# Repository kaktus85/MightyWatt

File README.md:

# MightyWatt
Resources for MightyWatt electronic load.
This repository contains all the available documentation and source files for MightyWatt electronic load project.
- a copy of this is also available on Google Drive: https://drive.google.com/folderview?id=0B7G3xJXZNLUpfnVWSEF0VTA3WkxmOUZ6U2pOcVNRdFloU2d0UzdjeE5NdHU3R0FZb3NNR2c&usp=sharing
- an easy to read description of the various folders is here: http://kaktuscircuits.blogspot.cz/2015/03/mightywatt-resource-page.html
- MightyWatt can be purchased through Tindie: https://www.tindie.com/products/Kaktus/mightywatt-kit-70w-electronic-load-for-arduino/

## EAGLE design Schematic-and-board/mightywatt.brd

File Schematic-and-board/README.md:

# Schematic and Board
- Cadsoft Eagle source files for the PCB of MightyWatt.
- A PNG schematic also included for a quick reference without having to install Eagle.

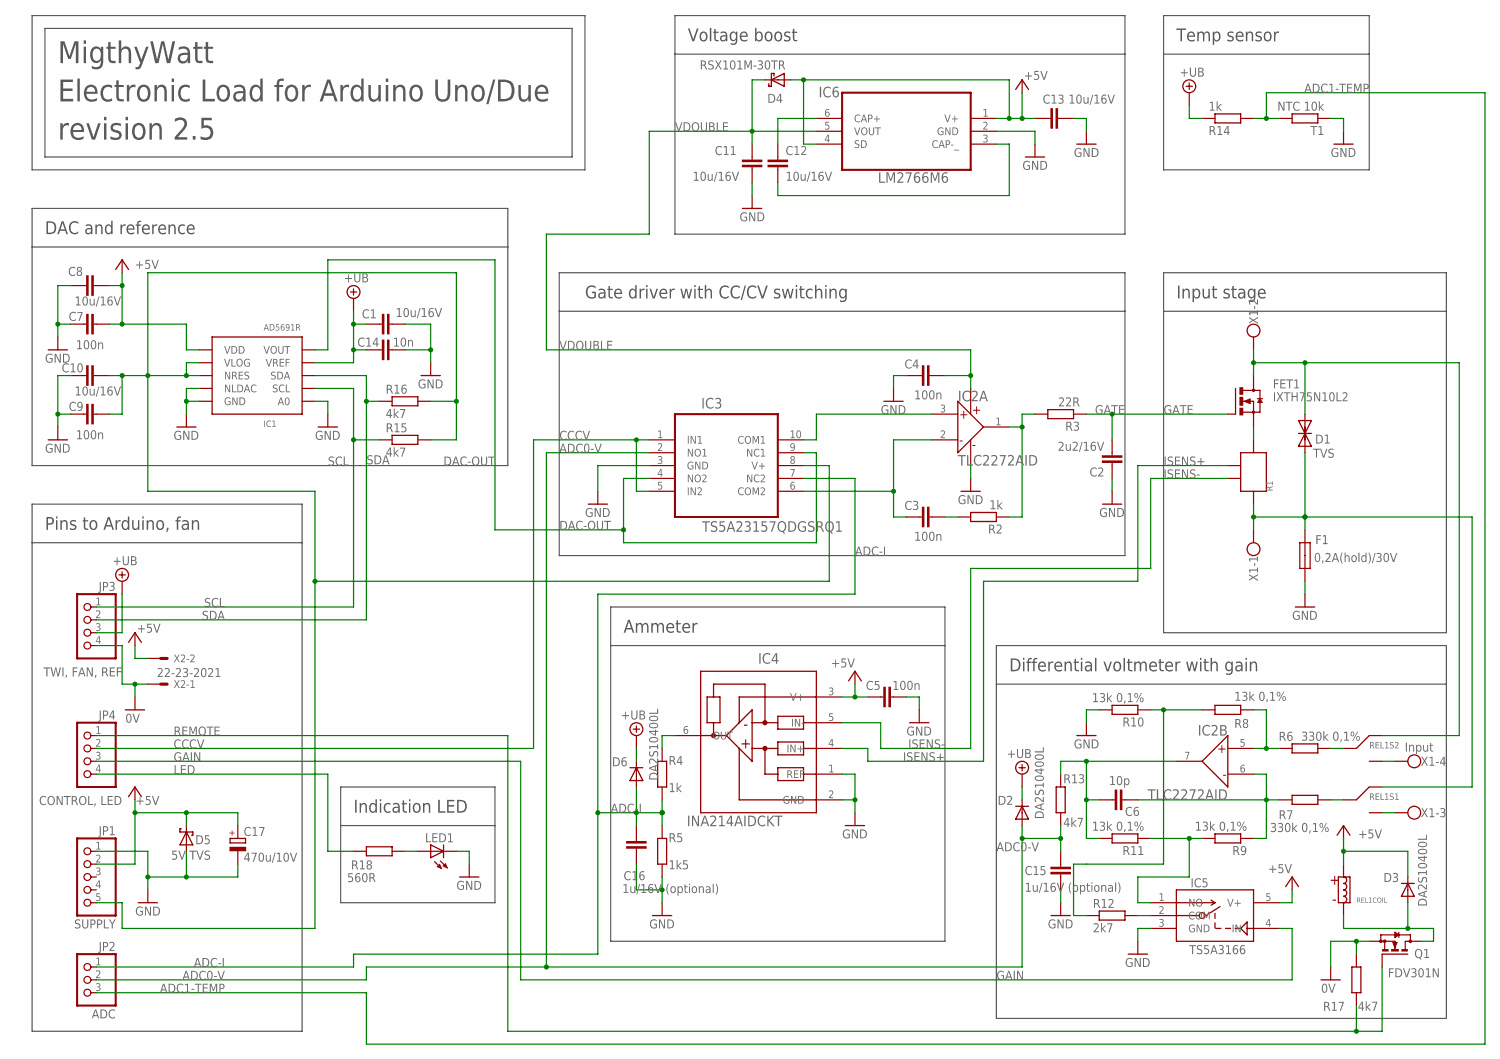
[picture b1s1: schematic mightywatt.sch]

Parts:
C1, C8, C10, C11, C12, C13: 10u/16V; C1206
C2: 2u2/16V; C1206
C3, C4, C5, C7, C9: 100n; C0603
C6: 10p; C0603
C14: 10n; C0805
C15, C16: 1u/16V (optional); C0603
C17: 470u/10V; SMC_E
D1: TVS; SMC
D2, D3, D6: DA2S10400L; SOD523
D4: RSX101M-30TR; SOD123
D5: 5V TVS; SMB
F1: 0,2A(hold)/30V; R1812
FET1: IXTH75N10L2; TO-247AD-H
IC1: AD5691RAD5691R; SOP50P490X110-10N
IC2: TLC2272AID; SOIC127P600X175-8N
IC3: TS5A23157QDGSRQ1; SOP50P490X110-10N
IC4: INA214AIDCKT; SOT65P210X110-6N; MPN INA214BIDCKT
IC5: TS5A3166; SC70-5
IC6: LM2766M6; SOT95P285X122-6N
JP1: SUPPLY; 1X05
JP2: ADC; 1X03
JP3: TWI, FAN, REF; 1X04
JP4: CONTROL, LED; 1X04
LED1: LEDCHIP-LED0805; CHIP-LED0805
Q1: BSS123; SOT23; PARTNAME FDV301N
R1: WSL3637; POWER-R-4TERM
R2, R4, R14: 1k; R0603
R3: 22R; R0603
R5: 1k5; R0603
R6, R7: 330k 0,1%; R0603
R8, R9, R10, R11: 13k 0,1%; R0603
R12: 2k7; R0603
R13, R15, R16, R17: 4k7; R0603
R18: 560R; R0603
REL1: IM03NS; IM03NS-NARROW-RELAY
T1: NTC 10k; R0402
X1: Input; W237-4
X2: 22-23-2021

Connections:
0V: JP3.4, Q1.2 (S), R17.1, X2.1
+5V: C5.1, C7.2, C8.2, C13.1, C17.+, D3.C, D4.A, D5.C, IC1.1 (VDD), IC4.3 (V+), IC5.5 (V+), IC6.1 (V+), IC6.4 (SD), JP1.2, REL1.P$1 (C+), X2.2
+UB: C1.1, C14.1, D2.C, D6.C, IC1.9 (VREF), JP3.3, R14.1
ADC0-V: C15.2, D2.A, IC3.2 (NO1), JP2.2, R13.1
ADC1-TEMP: JP2.3, R14.2, T1.2
ADC-I: C16.2, D6.A, IC3.7 (NC2), JP2.1, R4.2, R5.1
CCCV: IC3.1 (IN1), IC3.5 (IN2), JP4.2
DAC-OUT: IC1.10 (VOUT), IC3.4 (NO2), IC3.9 (NC1)
GAIN: IC5.4 (IN), JP4.3
GATE: C2.2, FET1.G, R3.1
GND: C1.2, C2.1, C4.1, C5.2, C7.1, C8.1, C9.1, C10.1, C11.2, C13.2, C14.2, C15.1, C16.1, C17.-, D5.A, F1.2, IC1.4 (NLDAC), IC1.5 (GND), IC1.6 (A0), IC2.4 (V-/GND), IC3.3 (GND), IC4.1 (REF), IC4.2 (GND), IC5.3 (GND), IC6.2 (GND), JP1.1, LED1.C, R5.2, R10.2, T1.1
IOREF: C9.2, C10.2, IC1.2 (VLOG), IC1.3 (NRES), IC3.8 (V+), JP1.5, R15.2, R16.2
ISENS+: IC4.4 (IN+), R1.SENSE2
ISENS-: IC4.5 (IN-), R1.SENSE1
LED: JP4.4, R18.1
unnamed: IC2.5 (IN+), R6.2, R8.1
unnamed: D1.A, F1.1, R1.POWER1, REL1.P$2 (NC), X1.1
unnamed: C6.1, IC2.6 (IN-), R7.2, R9.1
unnamed: D1.C, FET1.D, REL1.P$7 (NC), X1.2
unnamed: C12.1, IC6.6 (CAP+)
unnamed: C12.2, IC6.3 (CAP-_)
unnamed: R8.2, R10.1, R12.1
unnamed: REL1.P$4 (NO), X1.3
unnamed: REL1.P$5 (NO), X1.4
unnamed: FET1.S, R1.POWER2
unnamed: IC2.1 (OUT), R2.1, R3.2
unnamed: R6.1, REL1.P$6 (COM)
unnamed: IC5.2 (COM), R12.2
unnamed: IC5.1 (NO), R9.2, R11.1
unnamed: LED1.A, R18.2
unnamed: R7.1, REL1.P$3 (COM)
unnamed: C3.2, R2.2
unnamed: C3.1, IC2.2 (IN-), IC3.6 (COM2)
unnamed: C6.2, IC2.7 (OUT), R11.2, R13.2
unnamed: IC2.3 (IN+), IC3.10 (COM1)
unnamed: D3.A, Q1.3 (D), REL1.P$8 (C-)
R3: IC4.6 (OUT), R4.1
REMOTE: JP4.1, Q1.1 (G), R17.2
SCL: IC1.7 (SCL), JP3.1, R15.1
SDA: IC1.8 (SDA), JP3.2, R16.1
VDOUBLE: C4.2, C11.1, D4.C, IC2.8 (V+), IC6.5 (VOUT)

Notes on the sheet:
Voltage boost
DAC and reference
Temp sensor
Pins to Arduino, fan
Input stage
Ammeter
Differential voltmeter with gain
Gate driver with CC/CV switching
MigthyWatt Electronic Load for Arduino Uno/Due revision 2.5
Indication LED

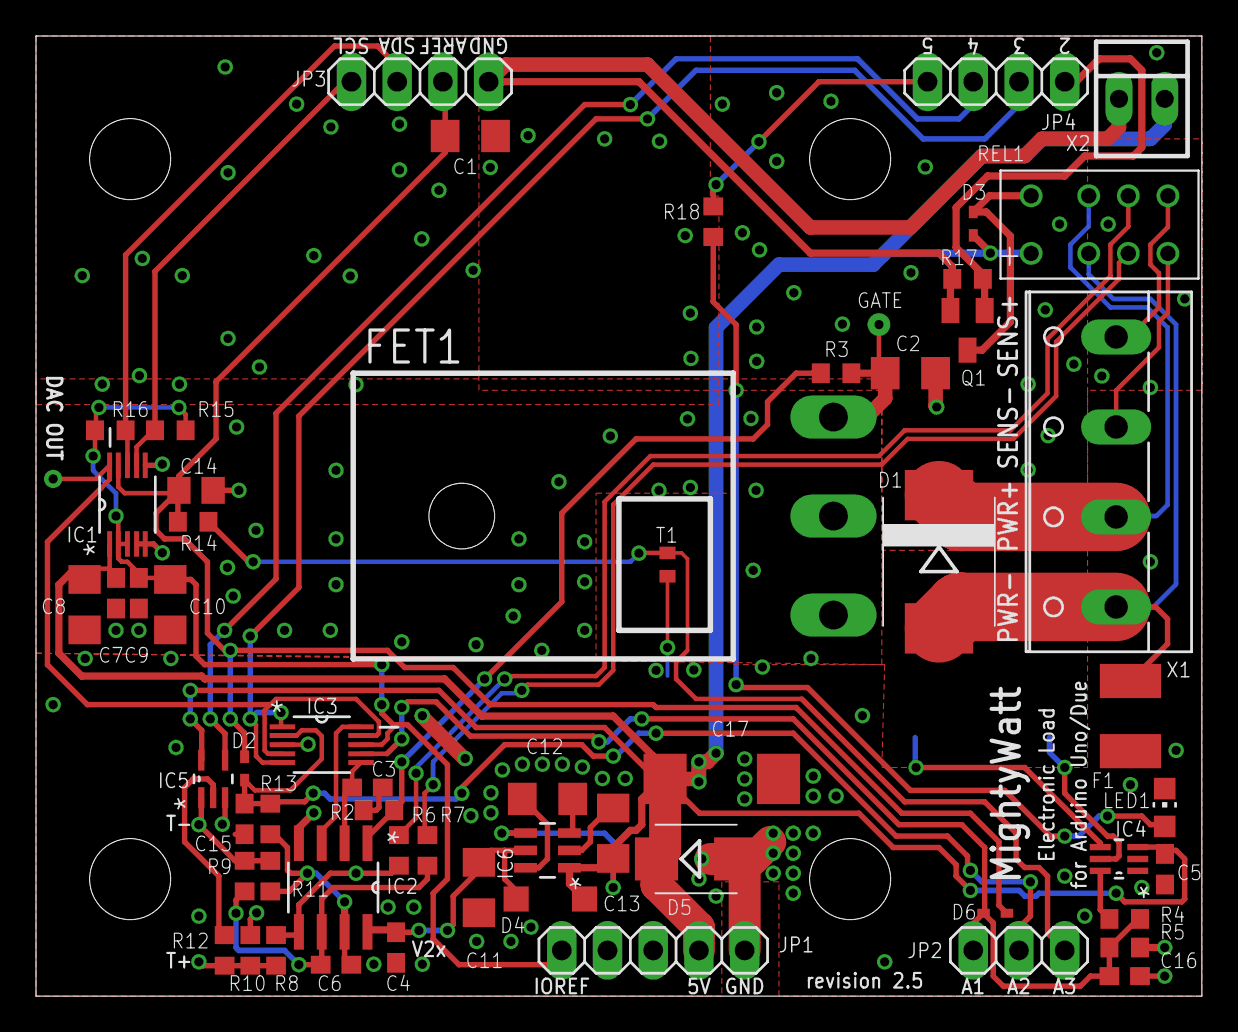
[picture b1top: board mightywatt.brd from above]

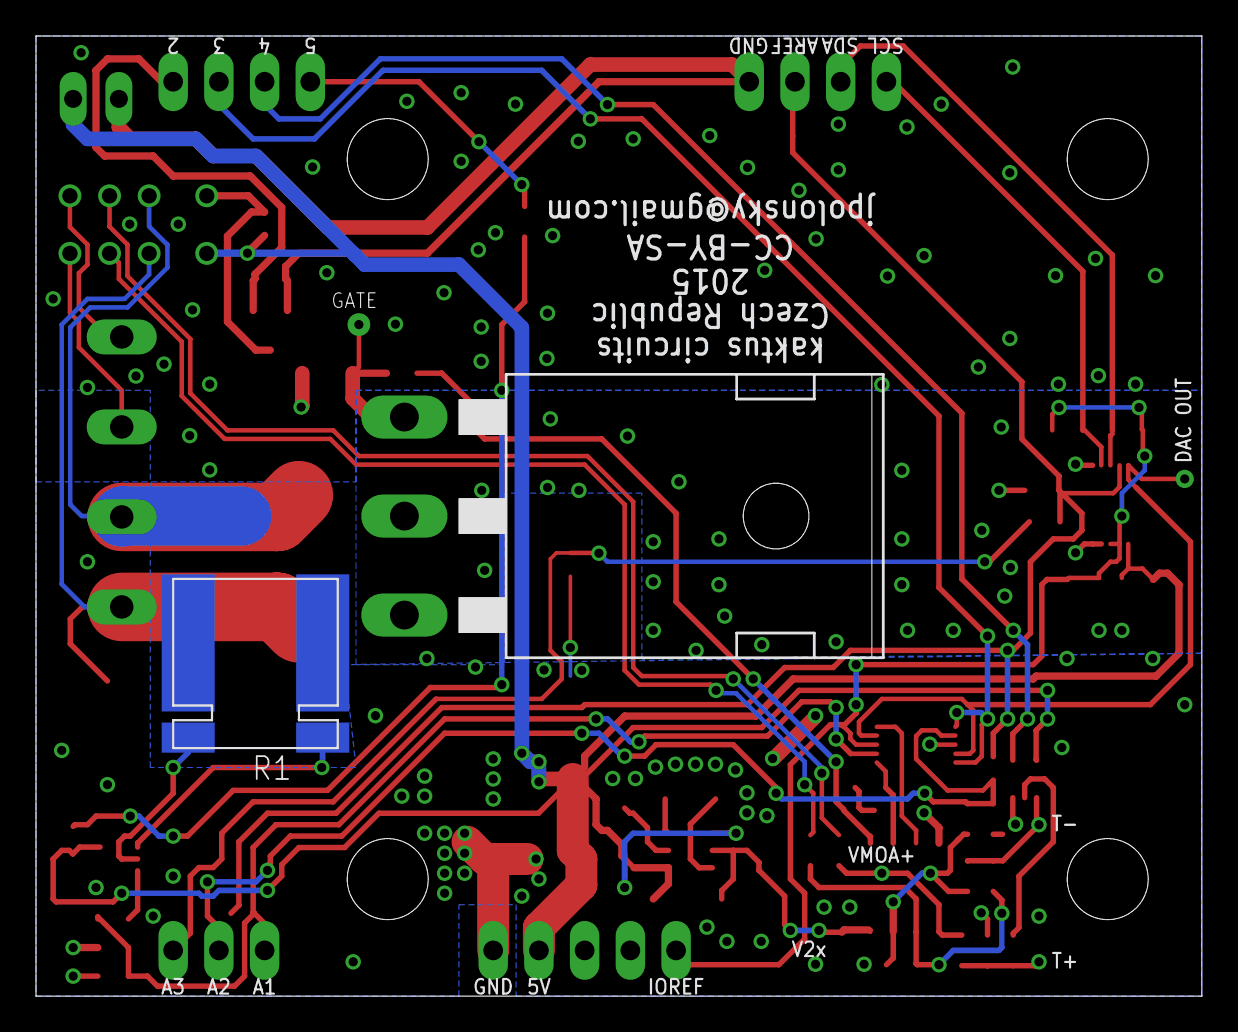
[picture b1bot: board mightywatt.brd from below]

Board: 2 copper layers, 64.8 x 53.3 mm, 59 parts (2 on the bottom side), 41 nets.

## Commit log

2016-06-29 Initial readme
2016-06-29 Case drawings first upload
2016-06-29 To create this directory
2016-06-29 Acrylic layered case
2016-06-29 Case drawings
2016-06-30 Create blank
2016-06-30 Sketch for the 4A version
    Sketch with approximate calibration values for the 4A version
    Please, calibrate with your Arduino (or whatever ADC you are using)
2016-06-30 Sketch for the 10A version
    Sketch with approximate calibration values for the 10A version
    Please, calibrate with your Arduino (or whatever ADC you're using)
2016-06-30 Sketch for the 20A version
    Sketch with approximate calibration values for the 20A version
    Please, calibrate with your Arduino (or whatever ADC you're using)
2016-06-30 Sketch for calibration
    Works with all versions of the current range
2016-06-30 PDF bill of materials
2016-06-30 Excel calibration aid
    Excel file to calculate and keep calibration values obtained from calibration sketch and external voltmeter/ammeter
2016-06-30 Guides for using MightyWatt
2016-06-30 Excel chart for MightyWatt
    Excel macro that can hook up to MightyWatt data file and display charts
2016-06-30 File rename and upload
2016-07-01 Rename LICENSE to LICENSE-SOFTWARE
2016-07-01 Create LICENSE-HARDWARE-AND-REST
2016-07-01 Create LICENSE
2016-07-01 MPPT algorithm change
    Added automatic current decrease on zero voltage. If the two previous
    actions were the same, the current change will be steeper (2 LSB instead
    of 1 LSB).
2016-07-01 Moved setDAC procedure to if block, will only execute if there is change
2016-08-20 Compatibility with Arduino Zero
2016-08-20 Added change log
2016-08-20 Updated LED current info
2016-08-23 Increased IADC_INTERCEPT integer size
    IADC_INTERCEPT is now 16-bit signed integer to accomodate Arduinos with
    larger offset.
2016-08-24 Automatic reset of DAC
    Added reset of DAC to the initialization routine
2016-08-24 Automatic reset of DAC
    Added automatic reset of DAC to initialization routine
2016-09-19 Fixed multiple showing of error messages
    Both for load-reported errors and for watchdog
2016-09-21 Added report on transient testing
2016-12-04 Better fit with Arduino Zero
2017-02-11 Added Integrator and statistics toolbox
    Integrators and statistics toolbox displays statistical information on
    measured values and can integrate charge and energy
2017-02-11 1.3.1.0 version release
2017-02-11 Fixed version numbers
2017-02-11 Statistics toolbox bug fix
2017-02-11 Added timestamp to statistics

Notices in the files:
Schematic-and-board/mightywatt.brd:
CC-BY-SA
